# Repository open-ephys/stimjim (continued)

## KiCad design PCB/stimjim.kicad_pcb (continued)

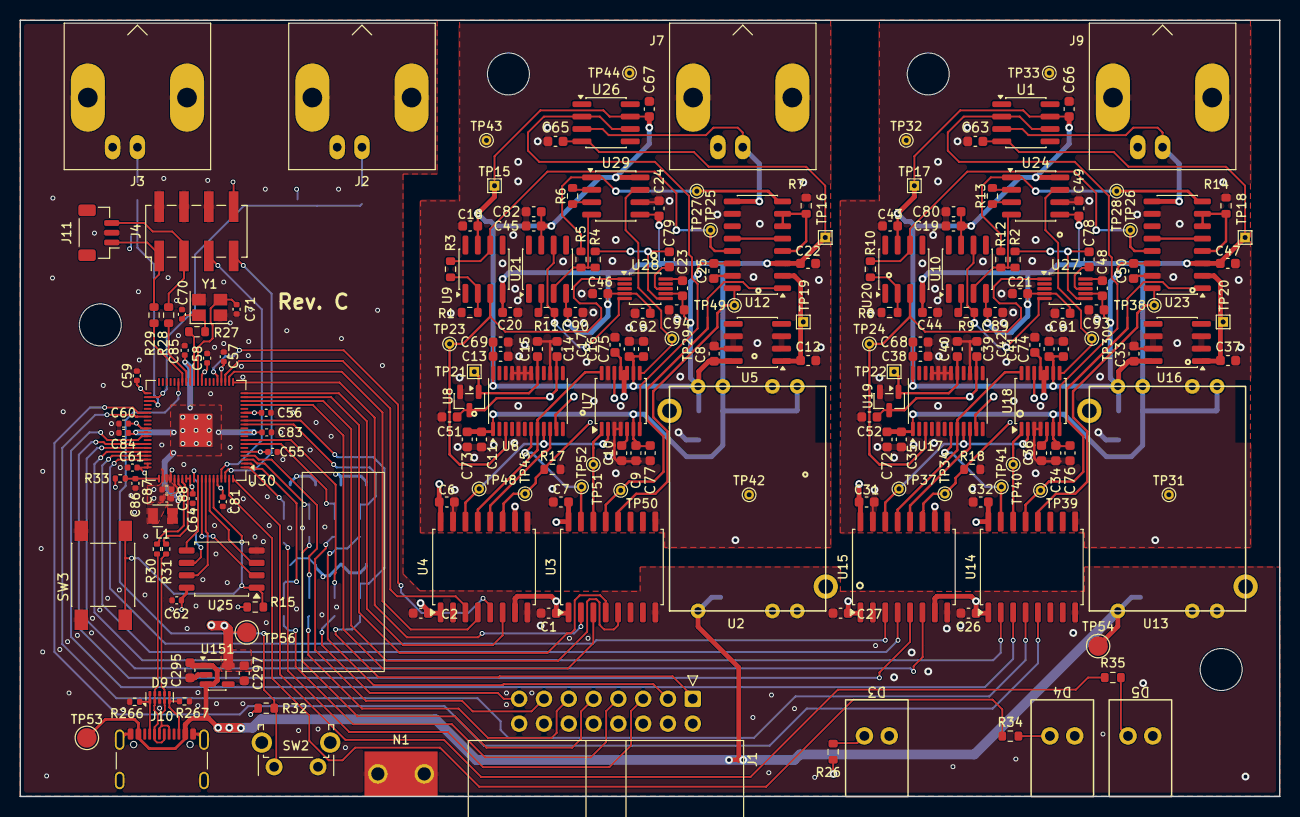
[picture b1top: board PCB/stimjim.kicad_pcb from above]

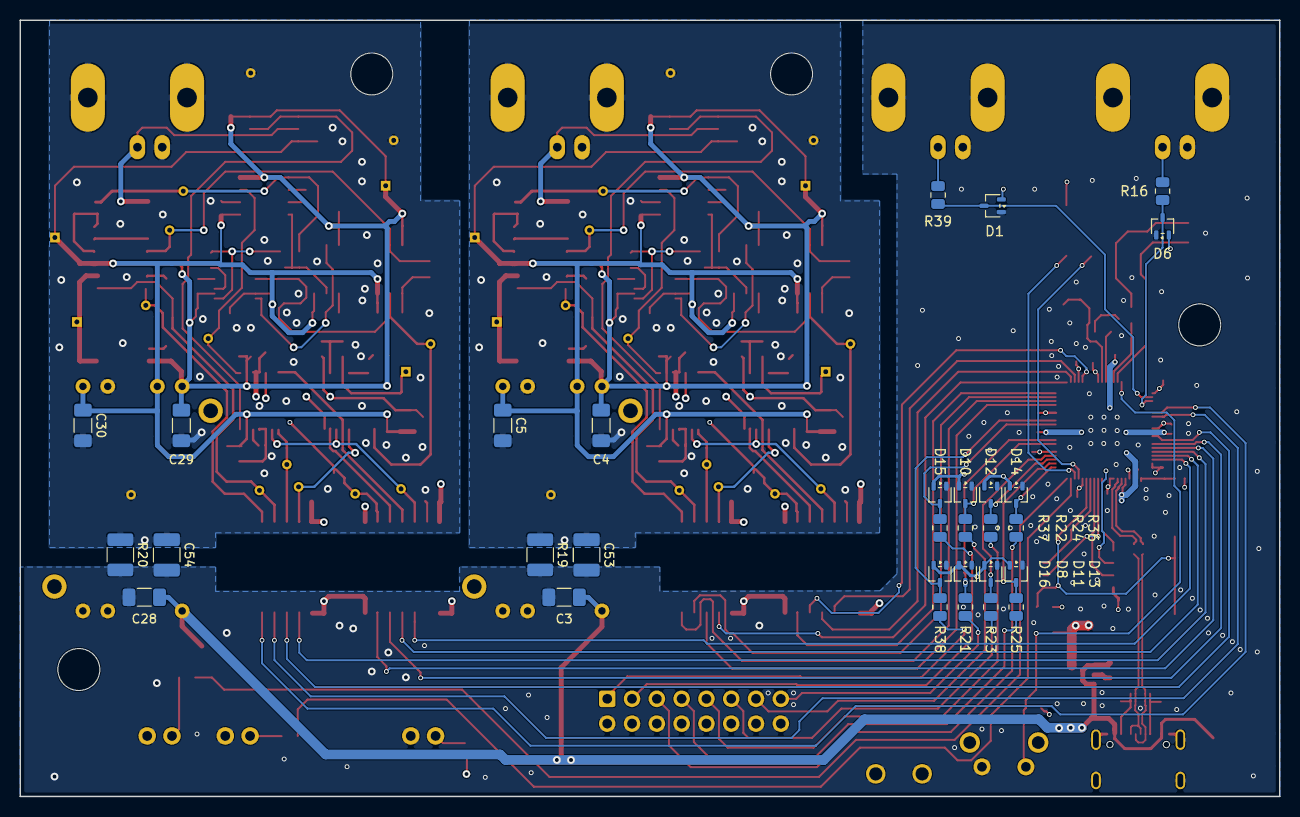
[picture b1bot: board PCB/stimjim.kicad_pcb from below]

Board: 4 copper layers, 129.0 x 79.5 mm, 235 parts (30 on the bottom side), 129 nets.

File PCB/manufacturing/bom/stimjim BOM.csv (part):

"#","Qty","Reference","Value","Tolerance","Footprint","TempCo","Voltage","DNP","OEPSPN","MPN","Description"
"1","40","C1,C2,C6,C7,C9,C11,C13,C14,C16,C17,C18,C20,C22,C23,C24,C25,C26,C27,C31,C32,C34,C35,C38,C39,C41,C42,C43,C44,C47,C48,C49,C50,C63,C65,C66,C67,C80,C82,C89,C90","0.1uF","","Capacitor_SMD:C_0603_1608Metric","","","","OEPS010009","GRM188R72A104KA35D","CAPACITOR:   SMD CER 0603 100nF 100V ±10% X7R   [GRM188R72A104KA35D] [SMD]"
"2","6","C3,C4,C5,C28,C29,C30","10uF","","Capacitor_SMD:C_1206_3216Metric_Pad1.33x1.80mm_HandSolder","","25V","","OEPS010094","GRT319R6YA106KE01D","CAPACITOR:   SMD CER 1206 10uF 35V ±10% X5R   [GRT319R6YA106KE01D] [SMD]"
"3","12","C8,C10,C12,C15,C33,C36,C37,C40,C51,C52,C295,C297","1uF","","Capacitor_SMD:C_0603_1608Metric","X5R","25V","","OEPS010022","CL10A105KA8NNNC","CAPACITOR:   SMD CER 0603 1uF 25V ±10% X5R   [CL10A105KA8NNNC] [SMD]"
"4","4","C19,C21,C45,C46","0.01uF","","Capacitor_SMD:C_0603_1608Metric","","","","OEPS010074","C1608X7R1H103K080AA","CAPACITOR:   SMD CER 0603 10nF 50V ±10% X7R   [C1608X7R1H103K080AA] [SMD]"
"5","2","C53,C54","2.2nF","","Capacitor_SMD:C_1210_3225Metric_Pad1.33x2.70mm_HandSolder","","","DNP","OEPS000000","DNP","DNP: Do Not Populate (DNI)"
"6","12","C55,C56,C57,C58,C59,C60,C61,C62,C64,C81,C83,C84","0.1uF","","Capacitor_SMD:C_0402_1005Metric","X7R","","","OEPS010050","C1005X7R1E104K050BB","CAPACITOR:   SMD CER 0402 100nF 25V ±10% X7R (OEPS H02 001)   [C1005X7R1E104K050BB] [SMD]"
"7","8","C68,C69,C72,C73,C74,C75,C76,C77","10uF","","Capacitor_SMD:C_0603_1608Metric","","","","OEPS010093","GRM188R6YA106MA73J","CAPACITOR:   SMD CER 0603 10uF 35V ±20% X5R   [GRM188R6YA106MA73J] [SMD]"
"8","2","C70,C71","22p","","Capacitor_SMD:C_0402_1005Metric","","","","OEPS010080","CL05C220JB51PNC","CAPACITOR:   SMD CER 0402 22pF 50V ±5% C0G/NP0   [CL05C220JB51PNC] [SMD]"
"9","2","C78,C79","10p","","Capacitor_SMD:C_0603_1608Metric","","","","OEPS010096","C0603C100J5GACTU","CAPACITOR:   SMD CER 0603 10pF 50V ±5% C0G   [C0603C100J5GACTU] [SMD]"
"10","4","C85,C86,C87,C88","4.7u","","Capacitor_SMD:C_0402_1005Metric","X5R","16V","","OEPS010097","KGM05CR51C475MH","CAPACITOR:   SMD CER 0402 4.7uF 16V ±20% X5R   [KGM05CR51C475MH] [SMD]"
"11","4","C91,C92,C93,C94","4.7u","","Capacitor_SMD:C_0603_1608Metric","","","","OEPS010047","GRM188R61E475KE11D","CAPACITOR:   SMD CER 0603 4.7uF 25V ±10% X5R (OEPS J05 009)   [GRM188R61E475KE11D] [SMD]"
"12","10","D1,D6,D8,D10,D11,D12,D13,D14,D15,D16","BAT54SW","","Package_TO_SOT_SMD:SOT-323_SC-70","","","","OEPS030056","BAT54SW","DIODE:   DIODE SCHOTTKY 30V 340mA ARRAY   [BAT54SW] [TH]"
"13","3","D3,D4,D5","LED","","open-ephys:LUMEX_SSF-LHXH100GD-01","","","","OEPS030055","SSF-LXH100GD-01","DIODE:   LED TH Green 565nm 20mA R/A   [SSF-LXH100GD-01] [TH]"
"14","1","D9","TPD4E05U06DQA","","Package_SON:USON-10_2.5x1.0mm_P0.5mm","","","","OEPS030037","TPD4E05U06DQAR","DIODE:   TVS DIODE 5.5VWM 14VC   [TPD4E05U06DQAR] [10-UFDFN]"
"15","1","J1","302-R161","","Connector_IDC:IDC-Header_2x08_P2.54mm_Horizontal","","","","OEPS070152","302-R161","CONNECTOR:   HEADER 2.54MM R/A 2x8POS   [302-R161] [TH]"
"16","4","J2,J3,J7,J9","0731375003","","Connector_Coaxial:BNC_Amphenol_B6252HB-NPP3G-50_Horizontal","","","","OEPS070151","0731375003","CONNECTOR:   BNC JACK 50ohm R/A   [0731375003] [TH]"
"17","1","J4","10129383-910002ALF","","Connector_PinHeader_2.54mm:PinHeader_2x04_P2.54mm_Vertical_SMD","","","DNP","OEPS070120","10129383-910002ALF","CONNECTOR:   HEADER VERT 2x5POS 2.54MM   [10129383-910002ALF] [SMD]"
"18","1","J10","USB4105-GF-A","","Connector_USB:USB_C_Receptacle_GCT_USB4105-xx-A_16P_TopMnt_Horizontal","","","","OEPS070105","USB4105-GF-A","CONNECTOR:   USB2.0 TYPE C 16P SMD R/A   [USB4105-GF-A] [SMD/TH]"
"19","1","J11","BM03B-SRSS-TB","","Connector_JST:JST_SH_BM03B-SRSS-TB_1x03-1MP_P1.00mm_Vertical","","","DNP","OEPS070121","BM03B-SRSS-TB","CONNECTOR:   HEADER VERT 3POS 1MM   [BM03B-SRSS-TB] [SMD]"
"20","1","L1","AOTA-B201610S3R3-101-T","","open-ephys:L_Abracon_2x1.6x1.0mm","","","","OEPS040036","AOTA-B201610S3R3-101-T","INDUCTOR:   FIXED INDUCTOR SMD 3.3uH 2.1A 140mΩ   [AOTA-B201610S3R3-101-T] [0806]"
"21","1","N1","SMTRAM3-7-5ET","","open-ephys:SMTRA_M3-7-5ET","","","","OEPS100089","SMTRAM3-7-5ET","OTHER:   SURFACE MOUNT R'ANGLE M3   [SMTRAM3-7-5ET] [Other]"
"22","2","R1,R8","5k","0.1%","Resistor_SMD:R_0603_1608Metric","","","","OEPS020263","RT0603BRE075KL","RESISTOR:   SMD 0603 5kΩ ±0.1% 0.100W   [RT0603BRE075KL] [SMD]"
"23","2","R2,R4","1.5k","0.1%","Resistor_SMD:R_0603_1608Metric","","","","OEPS020262","RG1608P-152-B-T5","RESISTOR:   SMD 0603 1.5kΩ ±0.1% 0.100W   [RG1608P-152-B-T5] [SMD]"
"24","2","R3,R10","10k","0.1%","Resistor_SMD:R_0603_1608Metric","","","","OEPS020235","RG1608P-103-B-T5","RESISTOR:   SMD 0603 10kΩ ±0.1% 0.100W   [RG1608P-103-B-T5] [SMD]"
"25","2","R5,R12","100","0.1%","Resistor_SMD:R_0603_1608Metric","","","","OEPS020232","RG1608P-101-B-T5","RESISTOR:   SMD 0603 100Ω ±0.1% 0.100W   [RG1608P-101-B-T5] [SMD]"
"26","2","R6,R13","1.8k","0.1%","Resistor_SMD:R_0603_1608Metric","","","","OEPS020261","RG1608P-182-B-T5 ","RESISTOR:   SMD 0603 1.8kΩ ±0.1% 0.100W   [RG1608P-182-B-T5] [SMD]"
"27","3","R7,R14,R27","1k","1%","Resistor_SMD:R_0603_1608Metric","","","","OEPS020215","RG1608P-102-B-T5","RESISTOR:   SMD 0603 1kΩ ±0.1% 0.100W   [RG1608P-102-B-T5] [SMD]"
"28","2","R9,R11","0","","Resistor_SMD:R_0603_1608Metric","","","","OEPS020151","RCS06030000Z0EA","RESISTOR:   SMD 0603 0Ω 1A   [RCS06030000Z0EA] [SMD]"
"29","4","R15,R17,R18,R32","10k","","Resistor_SMD:R_0603_1608Metric","","","","OEPS020133","RC0603FR-0710KL","RESISTOR:   SMD 0603 10kΩ ±1% 0.100W   [RC0603FR-0710KL] [SMD]"
"30","10","R16,R21,R22,R23,R24,R25,R36,R37,R38,R39","270","","Resistor_SMD:R_0805_2012Metric","","","","OEPS020024","CRCW0805270RFKEAHP","RESISTOR:   SMD 0805 270Ω ±1% 0.500W   [CRCW0805270RFKEAHP] [SMD]"
"31","2","R19,R20","2.2M","","Resistor_SMD:R_1210_3225Metric_Pad1.30x2.65mm_HandSolder","","","","OEPS020230","CRGCQ1210J2M2","RESISTOR:   SMD 1210 2.2MΩ ±5% 0.5W   [CRGCQ1210J2M2] [SMD]"
"32","3","R26,R34,R35","200","","Resistor_SMD:R_0603_1608Metric","","","","OEPS020141","RC0603FR-07200RL","RESISTOR:   SMD 0603 200Ω ±1% 0.100W (OEPS J30 017)   [RC0603FR-07200RL] [SMD]"
"33","2","R28,R29","100","1%","Resistor_SMD:R_0603_1608Metric","","","","OEPS020042","CRCW0603100RFKEAHP","RESISTOR:   SMD 0603 100Ω ±1% 0.333W   [CRCW0603100RFKEAHP] [SMD]"
"34","3","R30,R31,R33","27","","Resistor_SMD:R_0402_1005Metric","","","","OEPS020170","RMCF0402FT27R0","RESISTOR:   SMD 0402 27Ω ±1% 0.063W   [RMCF0402FT27R0] [SMD]"
"35","2","R266,R267","5.1k","1%","Resistor_SMD:R_0402_1005Metric","","","","OEPS020173","ERJ-2RKF5101X","RESISTOR:   SMD 0402 5.1kΩ ±1% 0.100W   [ERJ-2RKF5101X] [SMD]"
"36","1","SW2","PTS645VH58-2 LFS","","Button_Switch_THT:SW_Tactile_SPST_Angled_PTS645Vx58-2LFS","","","","OEPS070114","PTS645VH58-2 LFS","CONNECTOR:   SWITCH TACTILE SPST-NO 0.05A 12V   [PTS645VH58-2 LFS] [TH]"
"37","1","SW3","TS04-66-50-BK-160-SMT","","open-ephys:SAMESKY_TS04-66-XX-BK-XXX-SMT-XX","","","","OEPS070115","TS04-66-50-BK-160-SMT","CONNECTOR:   SWITCH TACTILE SPST-NO TOP ACTUATED   [TS04-66-50-BK-160-SMT] [SMD]"
"38","6","U1,U9,U10,U20,U21,U26","OPA197","","Package_SO:SOIC-8_3.9x4.9mm_P1.27mm","","","","OEPS080229","OPA197IDR","IC:   OPAMP GP 1 CIRCUIT   [OPA197IDR] [8-SOIC]"
"39","2","U2,U13","CC3-0512DF-E","","microstim:CC3-0512DF-E","","","","OEPS100043","CC3-0512DF-E","OTHER:   DC DC CONVERTER +/-12V TO +/-15V 3W   [CC3-0512DF-E] [Populated PCB]"
"40","2","U3,U14","ISO7760","","Package_SO:SOIC-16W_7.5x10.3mm_P1.27mm","","","","OEPS080228","ISO7760DWR","IC:   DIGITAL ISOLATOR 6 Channel    [ISO7760DWR] [16-SOIC]"
"41","2","U4,U15","ISO7741","","Package_SO:SOIC-16W_7.5x10.3mm_P1.27mm","","","","OEPS080227","ISO7741DWR","IC:   DIGITAL ISOLATOR 4 Channel    [ISO7741DWR] [16-SOIC]"
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
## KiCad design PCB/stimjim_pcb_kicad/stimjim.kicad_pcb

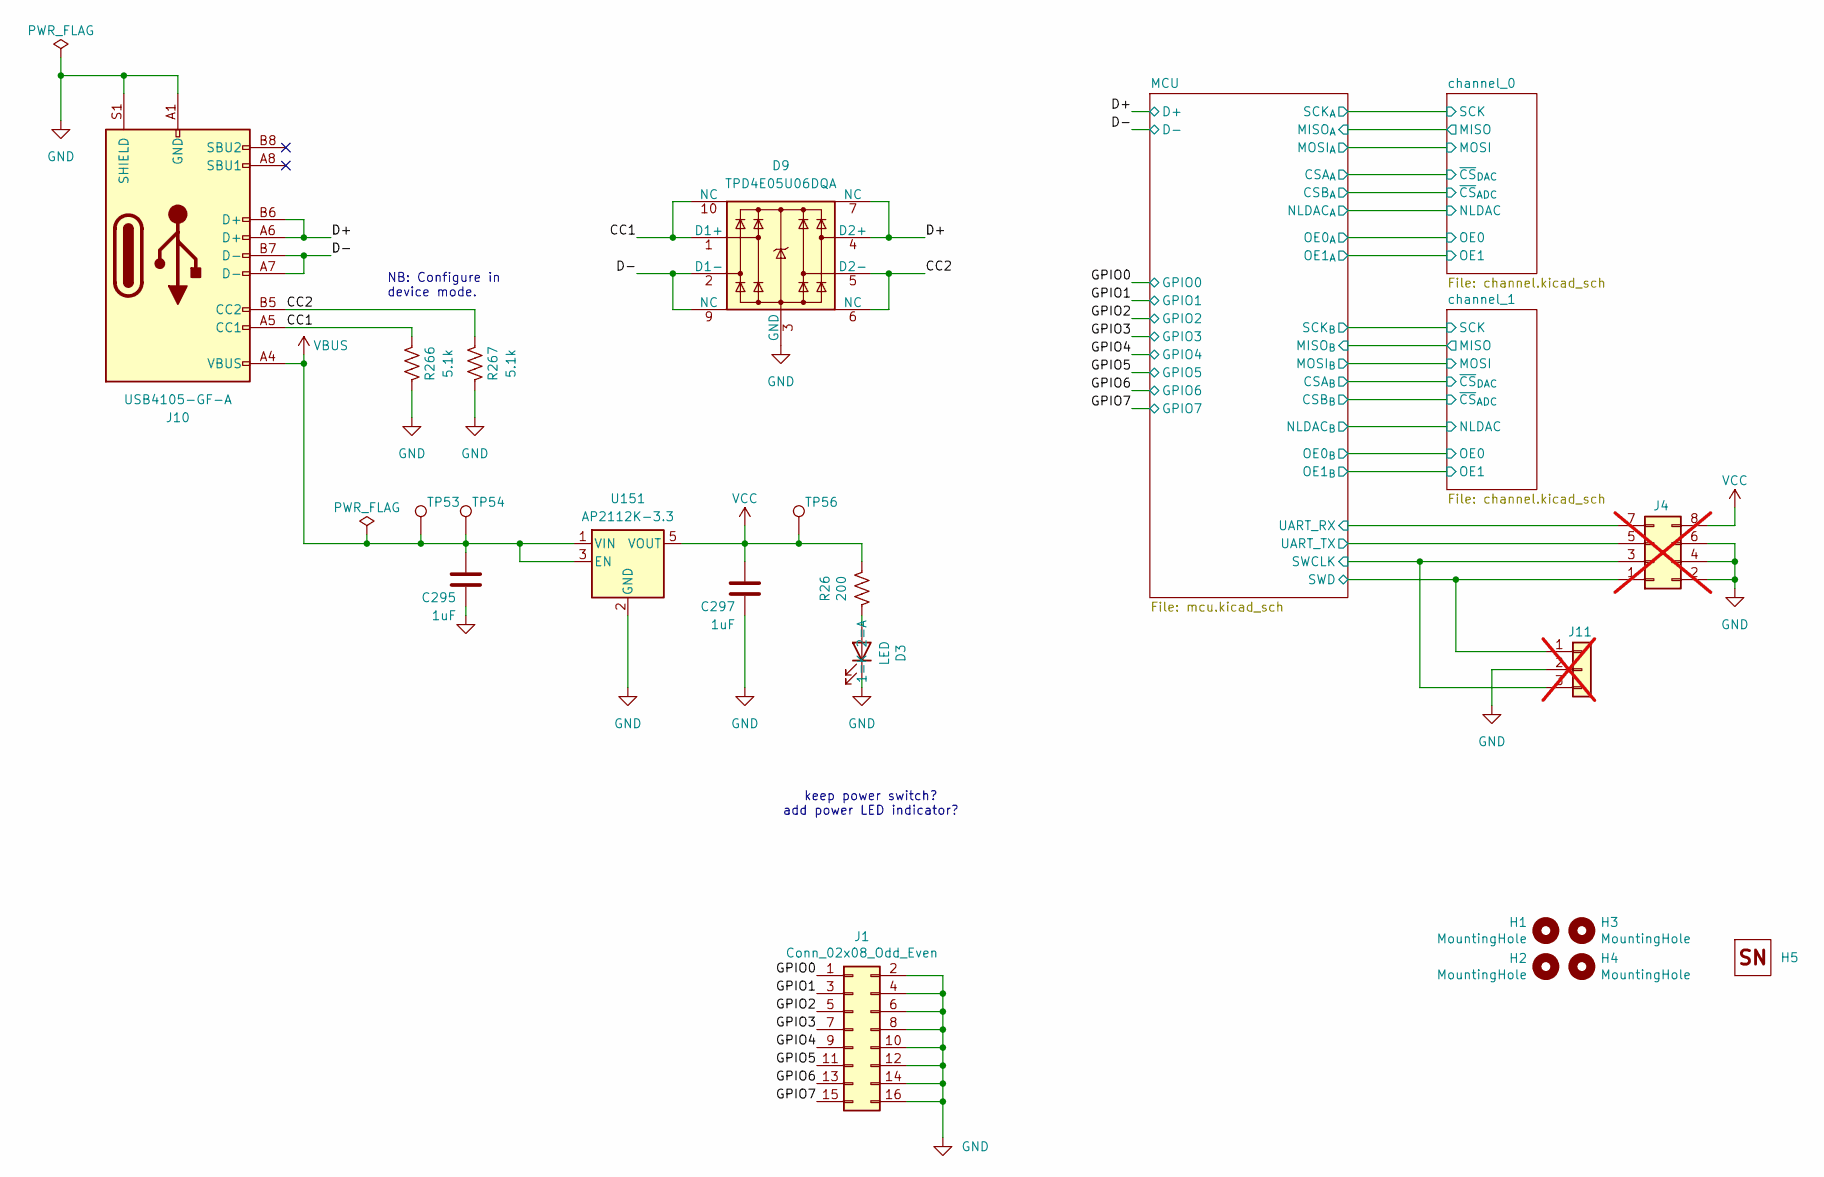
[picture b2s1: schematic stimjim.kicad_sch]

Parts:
C295, C297: 1uF; C_0603_1608Metric; Voltage 16V
D3: LED; LED_D5.0mm_Horizontal_O1.27mm_Z3.0mm_pinSwapped
D9: TPD4E05U06DQA; USON-10_2.5x1.0mm_P0.5mm
H1, H2, H3, H4: MountingHole; MountingHole_4.3mm_M4
H5: OEPS_SN-STICKER-8x20mm
J1: Conn_02x08_Odd_Even; IDC-Header_2x08_P2.54mm_Horizontal
J4: 10129383-910002ALF; PinHeader_2x04_P2.54mm_Vertical_SMD; not fitted
J10: USB4105-GF-A; USB_C_Receptacle_GCT_USB4105-xx-A_16P_TopMnt_Horizontal
J11: BM03B-SRSS-TB; JST_SH_BM03B-SRSS-TB_1x03-1MP_P1.00mm_Vertical; not fitted
R26: 200; R_0603_1608Metric
R266, R267: 5.1k; R_0402_1005Metric
TP53, TP54: GND; TestPoint_Pad_D2.0mm
TP56: VCC; TestPoint_Pad_D2.0mm
U151: AP2112K-3.3; SOT-23-5

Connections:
/CC1: D9.1 (D1+), D9.10 (NC), J10.A5 (CC1), R266.1
/CC2: D9.5 (D2-), D9.6 (NC), J10.B5 (CC2), R267.1
/D+: D9.4 (D2+), D9.7 (NC), J10.A6 (D+), J10.B6 (D+); also elsewhere on the board
/D-: D9.2 (D1-), D9.9 (NC), J10.A7 (D-), J10.B7 (D-); also elsewhere on the board
/GPIO0: J1.1; also elsewhere on the board
/GPIO1: J1.3; also elsewhere on the board
/GPIO2: J1.5; also elsewhere on the board
/GPIO3: J1.7; also elsewhere on the board
/GPIO4: J1.9; also elsewhere on the board
/GPIO5: J1.11; also elsewhere on the board
/GPIO6: J1.13; also elsewhere on the board
/GPIO7: J1.15; also elsewhere on the board
/MCU/SWCLK: J4.3, J11.3; also elsewhere on the board
/MCU/SWD: J4.1, J11.1; also elsewhere on the board
/MCU/UART_RX: J4.7; also elsewhere on the board
/MCU/UART_TX: J4.5; also elsewhere on the board
GND: C295.2, C297.2, D3.1 (K), D9.3 (GND), D9.8 (GND), J1.2, J1.4, J1.6, J1.8, J1.10, J1.12, J1.14, J1.16, J4.2, J4.4, J4.6, J10.A1 (GND), J10.A12 (GND), J10.B1 (GND), J10.B12 (GND), J10.S1 (SHIELD), J11.2, R266.2, R267.2, U151.2 (GND); also elsewhere on the board
unnamed: D3.2 (A), R26.2
VBUS: C295.1, J10.A4 (VBUS), J10.A9 (VBUS), J10.B4 (VBUS), J10.B9 (VBUS), TP53.1, TP54.1, U151.1 (VIN), U151.3 (EN); also elsewhere on the board
VCC: C297.1, J4.8, R26.1, TP56.1, U151.5 (VOUT); also elsewhere on the board

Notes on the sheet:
NB: Configure in device mode.
keep power switch? add power LED indicator?

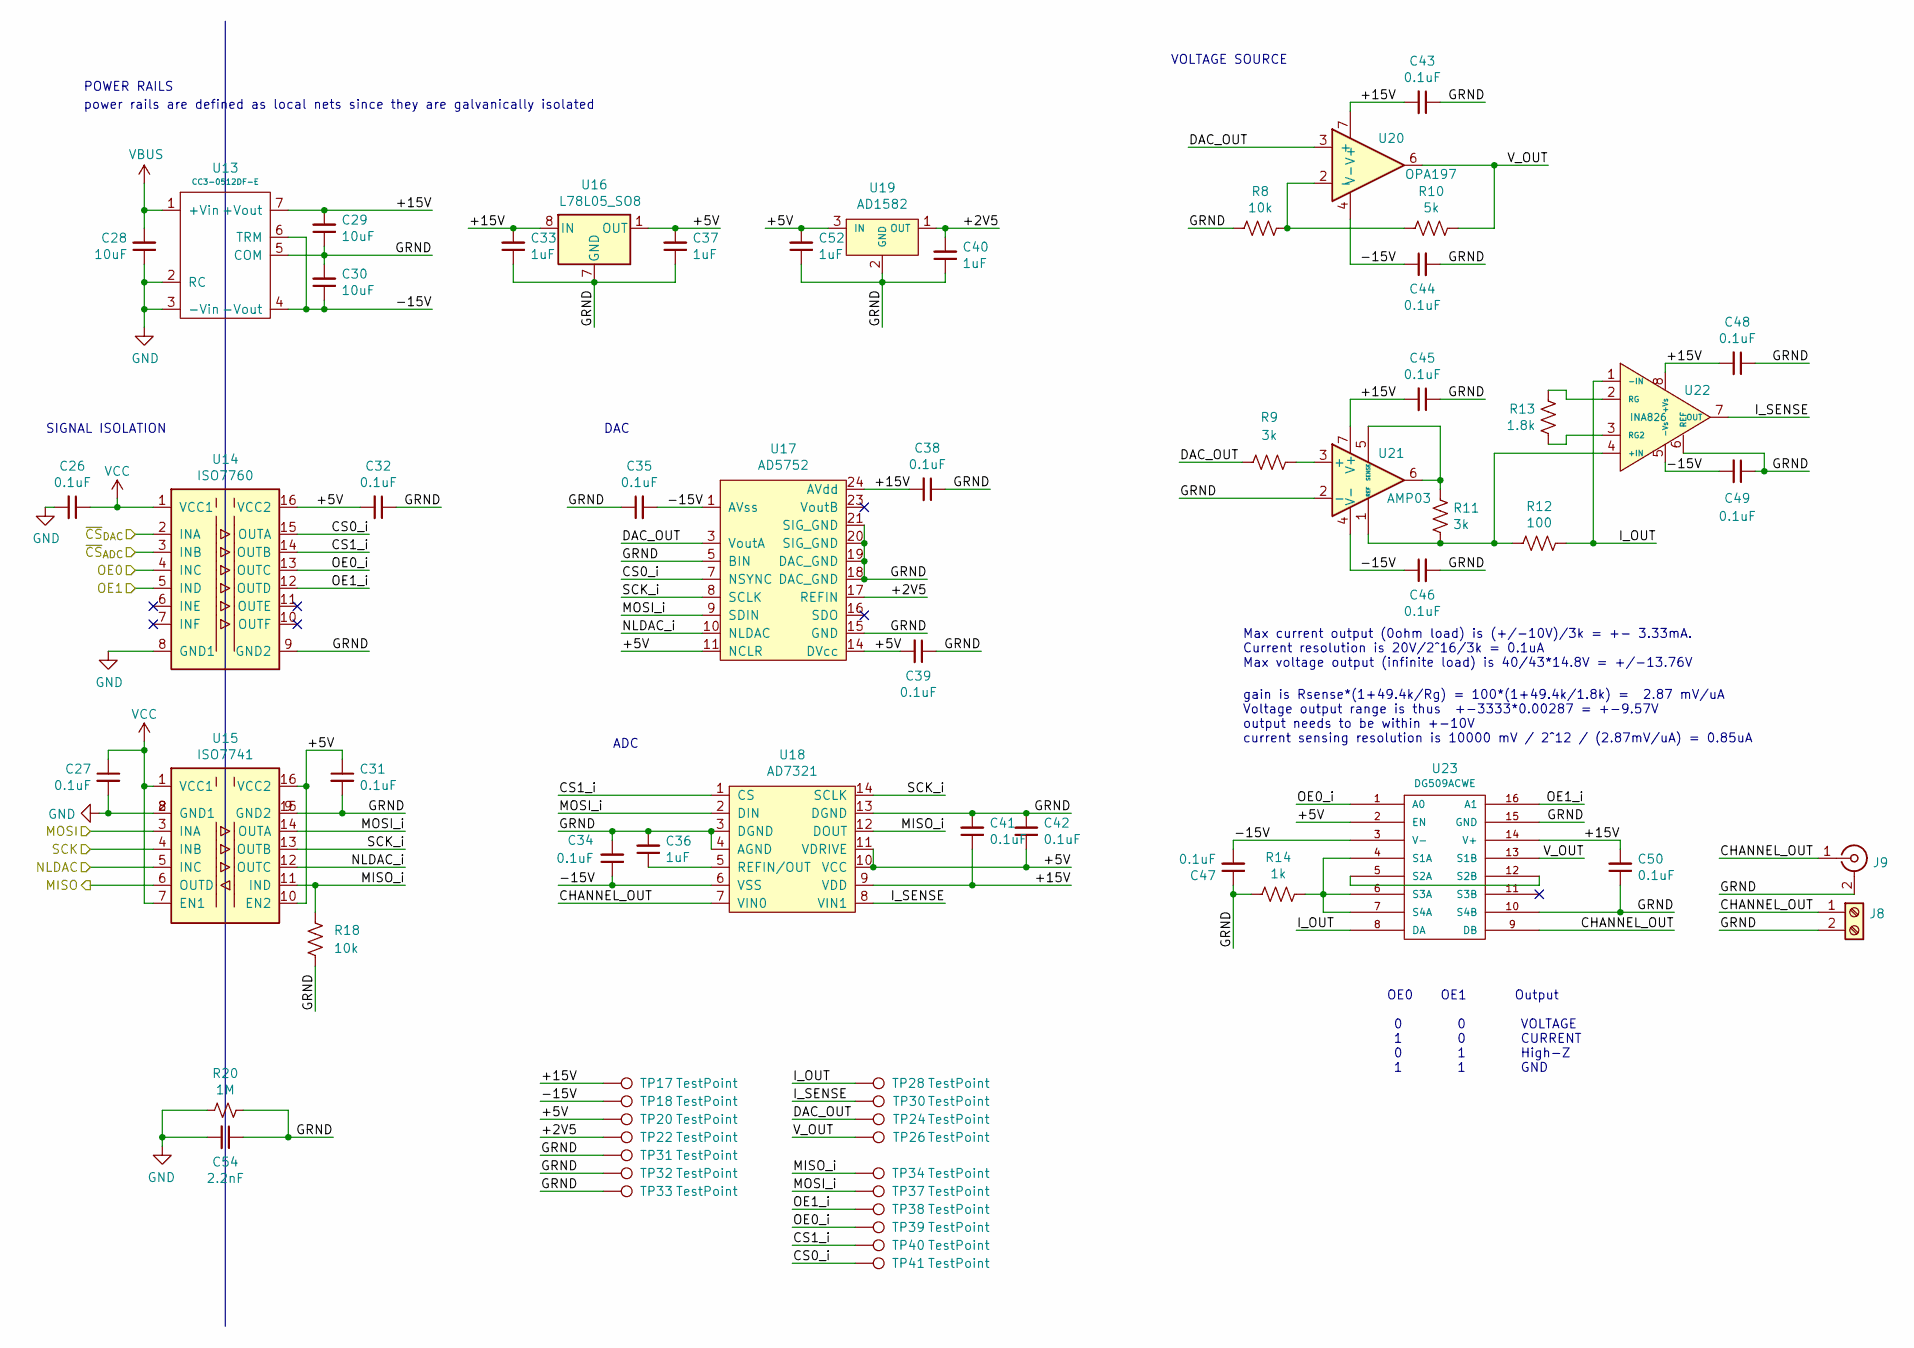
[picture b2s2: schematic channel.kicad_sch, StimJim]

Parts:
C26, C27, C31, C32, C34, C35, C38, C39, C41, C42, C43, C44, C45, C46, C47, C48, C49, C50: 0.1uF; C_0603_1608Metric
C28, C29, C30: 10uF; C_1206_3216Metric_Pad1.33x1.80mm_HandSolder
C33, C36, C37, C40, C52: 1uF; C_0603_1608Metric
C54: 2.2nF; C_1210_3225Metric_Pad1.33x2.70mm_HandSolder
J8: Screw_Terminal_01x02; 1-2834016-2 _TERM_BLK_2P_SIDE_ENT_2.54MM_PCB
J9: Conn_Coaxial; BNC_Amphenol_B6252HB-NPP3G-50_Horizontal
R8, R18: 10k; R_0603_1608Metric
R9, R11: 3k; R_0603_1608Metric
R10: 5k; R_0603_1608Metric
R12: 100; R_0603_1608Metric
R13: 1.8k; R_0603_1608Metric
R14: 1k; R_0603_1608Metric
R20: 1M; R_1210_3225Metric_Pad1.30x2.65mm_HandSolder
TP17, TP18, TP20, TP22: TestPoint; TestPoint_THTPad_1.0x1.0mm_Drill0.5mm
TP24, TP26, TP28, TP30, TP31, TP32, TP33, TP34, TP37, TP38, TP39, TP40, TP41: TestPoint; TestPoint_THTPad_D1.0mm_Drill0.5mm
U13: CC3-0512DF-E
U14: ISO7760; SOIC-16W_7.5x10.3mm_P1.27mm
U15: ISO7741; SOIC-16W_7.5x10.3mm_P1.27mm
U16: L78L05_SO8; SOIC-8_3.9x4.9mm_P1.27mm
U17: AD5752; TSSOP-24_4.4x7.8mm_P0.65mm
U18: AD7321; TSSOP-14_4.4x5mm_P0.65mm
U19: AD1582; SOT-23
U20: OPA197; SOIC-8_3.9x4.9mm_P1.27mm
U21: AMP03; SOIC-8_3.9x4.9mm_P1.27mm
U22: INA826; SOIC-8_3.9x4.9mm_P1.27mm
U23: DG509ACWE; SO-16_3.9x9.9mm_P1.27mm

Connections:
/MCU/CSA_{A}: U14.2 (INA); also elsewhere on the board
/MCU/CSB_{A}: U14.3 (INB); also elsewhere on the board
/MCU/MISO_{A}: U15.6 (OUTD); also elsewhere on the board
/MCU/MOSI_{A}: U15.3 (INA); also elsewhere on the board
/MCU/NLDAC_{A}: U15.5 (INC); also elsewhere on the board
/MCU/OE0_{A}: U14.4 (INC); also elsewhere on the board
/MCU/OE1_{A}: U14.5 (IND); also elsewhere on the board
/MCU/SCK_{A}: U15.4 (INB); also elsewhere on the board
/channel_0/+2V5: C40.2, TP22.1, U17.17 (REFIN), U19.1 (OUT)
/channel_0/+5V: C31.1, C32.2, C37.2, C39.2, C42.1, C52.2, TP20.1, U14.16 (VCC2), U15.10 (EN2), U15.16 (VCC2), U16.1 (OUT), U17.11 (NCLR), U17.14 (DVcc), U18.10 (VCC), U18.11 (VDRIVE), U19.3 (IN), U23.2 (EN)
/channel_0/+15V: C29.2, C33.2, C38.2, C41.1, C43.2, C45.2, C48.2, C50.2, TP17.1, U13.7 (+Vout), U16.8 (IN), U17.24 (AVdd), U18.9 (VDD), U20.7 (V+), U21.7 (V+), U22.8 (+Vs), U23.14 (V+)
/channel_0/-15V: C30.1, C34.1, C35.2, C44.1, C46.1, C47.2, C49.2, TP18.1, U13.4 (-Vout), U13.6 (TRM), U17.1 (AVss), U18.6 (VSS), U20.4 (V-), U21.4 (V-), U22.5 (-Vs), U23.3 (V-)
/channel_0/CHANNEL_OUT: J8.1, J9.1 (In), U18.7 (VIN0), U23.9 (DB)
/channel_0/CS0_i: TP41.1, U14.15 (OUTA), U17.7 (NSYNC)
/channel_0/CS1_i: TP40.1, U14.14 (OUTB), U18.1 (CS)
/channel_0/DAC_OUT: R9.2, TP24.1, U17.3 (VoutA), U20.3 (+)
/channel_0/GRND: C29.1, C30.2, C31.2, C32.1, C33.1, C34.2, C35.1, C36.2, C37.1, C38.1, C39.1, C40.1, C41.2, C42.2, C43.1, C44.2, C45.1, C46.2, C47.1, C48.1, C49.1, C50.1, C52.1, C54.1, J8.2, J9.2 (Ext), R8.1, R14.1, R18.1, R20.1, TP31.1, TP32.1, TP33.1, U13.5 (COM), U14.9 (GND2), U15.9 (GND2), U15.15 (GND2), U16.2 (GND), U16.3 (GND), U16.6 (GND), U16.7 (GND), U17.5 (BIN), U17.15 (GND), U17.18 (DAC_GND), U17.19 (DAC_GND), U17.20 (SIG_GND), U17.21 (SIG_GND), U18.3 (DGND), U18.4 (AGND), U18.13 (DGND), U19.2 (GND), U21.2 (-), U22.6 (REF), U23.10 (S4B), U23.15 (GND)
/channel_0/I_OUT: R12.2, TP28.1, U22.1 (-IN), U23.8 (DA)
/channel_0/I_SENSE: TP30.1, U18.8 (VIN1), U22.7 (OUT)
/channel_0/MISO_i: R18.2, TP34.1, U15.11 (IND), U18.12 (DOUT)
/channel_0/MOSI_i: TP37.1, U15.14 (OUTA), U17.9 (SDIN), U18.2 (DIN)
/channel_0/NLDAC_i: U15.12 (OUTC), U17.10 (NLDAC)
/channel_0/OE0_i: TP39.1, U14.13 (OUTC), U23.1 (A0)
/channel_0/OE1_i: TP38.1, U14.12 (OUTD), U23.16 (A1)
/channel_0/SCK_i: U15.13 (OUTB), U17.8 (SCLK), U18.14 (SCLK)
/channel_0/V_OUT: R10.2, TP26.1, U20.6, U23.13 (S1B)
GND: C26.2, C27.2, C28.1, C54.2, R20.2, U13.2 (RC), U13.3 (-Vin), U14.8 (GND1), U15.2 (GND1), U15.8 (GND1); also elsewhere on the board
unnamed: C36.1, U18.5 (REFIN/OUT)
unnamed: R8.2, R10.1, U20.2 (-)
unnamed: R9.1, U21.3 (+)
unnamed: R11.1, R12.1, U21.1 (REF), U22.4 (+IN)
unnamed: R11.2, U21.5 (SENSE), U21.6
unnamed: R13.1, U22.3 (RG2)
unnamed: R13.2, U22.2 (RG)
unnamed: R14.2, U23.4 (S1A), U23.6 (S3A), U23.7 (S4A)
unnamed: U23.5 (S2A), U23.12 (S2B)
VBUS: C28.2, U13.1 (+Vin); also elsewhere on the board
VCC: C26.1, C27.1, U14.1 (VCC1), U15.1 (VCC1), U15.7 (EN1); also elsewhere on the board

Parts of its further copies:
C1, C2, C6, C7, C9, C11, C13, C14, C16, C17, C18, C19, C20, C21, C22, C23, C24, C25: 0.1uF; C_0603_1608Metric
C3, C4, C5: 10uF; C_1206_3216Metric_Pad1.33x1.80mm_HandSolder
C8, C10, C12, C15, C51: 1uF; C_0603_1608Metric
C53: 2.2nF; C_1210_3225Metric_Pad1.33x2.70mm_HandSolder
J6: Screw_Terminal_01x02; 1-2834016-2 _TERM_BLK_2P_SIDE_ENT_2.54MM_PCB
J7: Conn_Coaxial; BNC_Amphenol_B6252HB-NPP3G-50_Horizontal
R1, R17: 10k; R_0603_1608Metric
R2, R4: 3k; R_0603_1608Metric
R3: 5k; R_0603_1608Metric
R5: 100; R_0603_1608Metric
R6: 1.8k; R_0603_1608Metric
R7: 1k; R_0603_1608Metric
R19: 1M; R_1210_3225Metric_Pad1.30x2.65mm_HandSolder
TP15, TP16, TP19, TP21: TestPoint; TestPoint_THTPad_1.0x1.0mm_Drill0.5mm
TP23, TP25, TP27, TP29, TP42, TP43, TP44, TP45, TP48, TP49, TP50, TP51, TP52: TestPoint; TestPoint_THTPad_D1.0mm_Drill0.5mm
U2: CC3-0512DF-E
U3: ISO7760; SOIC-16W_7.5x10.3mm_P1.27mm
U4: ISO7741; SOIC-16W_7.5x10.3mm_P1.27mm
U5: L78L05_SO8; SOIC-8_3.9x4.9mm_P1.27mm
U6: AD5752; TSSOP-24_4.4x7.8mm_P0.65mm
U7: AD7321; TSSOP-14_4.4x5mm_P0.65mm
U8: AD1582; SOT-23
U9: OPA197; SOIC-8_3.9x4.9mm_P1.27mm
U10: AMP03; SOIC-8_3.9x4.9mm_P1.27mm
U11: INA826; SOIC-8_3.9x4.9mm_P1.27mm
U12: DG509ACWE; SO-16_3.9x9.9mm_P1.27mm

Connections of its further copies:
/MCU/CSA_{B}: U3.2 (INA); also elsewhere on the board
/MCU/CSB_{B}: U3.3 (INB); also elsewhere on the board
/MCU/MISO_{B}: U4.6 (OUTD); also elsewhere on the board
/MCU/MOSI_{B}: U4.3 (INA); also elsewhere on the board
/MCU/NLDAC_{B}: U4.5 (INC); also elsewhere on the board
/MCU/OE0_{B}: U3.4 (INC); also elsewhere on the board
/MCU/OE1_{B}: U3.5 (IND); also elsewhere on the board
/MCU/SCK_{B}: U4.4 (INB); also elsewhere on the board
/channel_1/+2V5: C15.2, TP21.1, U6.17 (REFIN), U8.1 (OUT)
/channel_1/+5V: C6.1, C7.2, C12.2, C14.2, C17.1, C51.2, TP19.1, U3.16 (VCC2), U4.10 (EN2), U4.16 (VCC2), U5.1 (OUT), U6.11 (NCLR), U6.14 (DVcc), U7.10 (VCC), U7.11 (VDRIVE), U8.3 (IN), U12.2 (EN)
/channel_1/+15V: C4.2, C8.2, C13.2, C16.1, C18.2, C19.2, C23.2, C25.2, TP15.1, U2.7 (+Vout), U5.8 (IN), U6.24 (AVdd), U7.9 (VDD), U9.7 (V+), U10.7 (V+), U11.8 (+Vs), U12.14 (V+)
/channel_1/-15V: C5.1, C9.1, C11.2, C20.1, C21.1, C22.2, C24.2, TP16.1, U2.4 (-Vout), U2.6 (TRM), U6.1 (AVss), U7.6 (VSS), U9.4 (V-), U10.4 (V-), U11.5 (-Vs), U12.3 (V-)
/channel_1/CHANNEL_OUT: J6.1, J7.1 (In), U7.7 (VIN0), U12.9 (DB)
/channel_1/CS0_i: TP52.1, U3.15 (OUTA), U6.7 (NSYNC)
/channel_1/CS1_i: TP51.1, U3.14 (OUTB), U7.1 (CS)
/channel_1/DAC_OUT: R2.2, TP23.1, U6.3 (VoutA), U9.3 (+)
/channel_1/GRND: C4.1, C5.2, C6.2, C7.1, C8.1, C9.2, C10.2, C11.1, C12.1, C13.1, C14.1, C15.1, C16.2, C17.2, C18.1, C19.1, C20.2, C21.2, C22.1, C23.1, C24.1, C25.1, C51.1, C53.1, J6.2, J7.2 (Ext), R1.1, R7.1, R17.1, R19.1, TP42.1, TP43.1, TP44.1, U2.5 (COM), U3.9 (GND2), U4.9 (GND2), U4.15 (GND2), U5.2 (GND), U5.3 (GND), U5.6 (GND), U5.7 (GND), U6.5 (BIN), U6.15 (GND), U6.18 (DAC_GND), U6.19 (DAC_GND), U6.20 (SIG_GND), U6.21 (SIG_GND), U7.3 (DGND), U7.4 (AGND), U7.13 (DGND), U8.2 (GND), U10.2 (-), U11.6 (REF), U12.10 (S4B), U12.15 (GND)
/channel_1/I_OUT: R5.2, TP27.1, U11.1 (-IN), U12.8 (DA)
/channel_1/I_SENSE: TP29.1, U7.8 (VIN1), U11.7 (OUT)
/channel_1/MISO_i: R17.2, TP45.1, U4.11 (IND), U7.12 (DOUT)
/channel_1/MOSI_i: TP48.1, U4.14 (OUTA), U6.9 (SDIN), U7.2 (DIN)
/channel_1/NLDAC_i: U4.12 (OUTC), U6.10 (NLDAC)
/channel_1/OE0_i: TP50.1, U3.13 (OUTC), U12.1 (A0)
/channel_1/OE1_i: TP49.1, U3.12 (OUTD), U12.16 (A1)
/channel_1/SCK_i: U4.13 (OUTB), U6.8 (SCLK), U7.14 (SCLK)
/channel_1/V_OUT: R3.2, TP25.1, U9.6, U12.13 (S1B)
GND: C1.2, C2.2, C3.1, C53.2, R19.2, U2.2 (RC), U2.3 (-Vin), U3.8 (GND1), U4.2 (GND1), U4.8 (GND1); also elsewhere on the board
unnamed: C10.1, U7.5 (REFIN/OUT)
unnamed: R1.2, R3.1, U9.2 (-)
unnamed: R2.1, U10.3 (+)
unnamed: R4.1, R5.1, U10.1 (REF), U11.4 (+IN)
unnamed: R4.2, U10.5 (SENSE), U10.6
unnamed: R6.1, U11.3 (RG2)
unnamed: R6.2, U11.2 (RG)
unnamed: R7.2, U12.4 (S1A), U12.6 (S3A), U12.7 (S4A)
unnamed: U12.5 (S2A), U12.12 (S2B)
VBUS: C3.2, U2.1 (+Vin); also elsewhere on the board
VCC: C1.1, C2.1, U3.1 (VCC1), U4.1 (VCC1), U4.7 (EN1); also elsewhere on the board

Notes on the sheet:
power rails are defined as local nets since they are galvanically isolated
ADC
gain is Rsense*(1+49.4k/Rg) = 100*(1+49.4k/1.8k) = 2.87 mV/uA Voltage output range is thus +-3333*0.00287 = +-9.57V output needs to be within +-10V current sensing resolution is 10000 mV / 2^12 / (2.87mV/uA) = 0.85uA
OE0 OE1 Output 0 0 VOLTAGE 1 0 CURRENT 0 1 High-Z 1 1 GND
SIGNAL ISOLATION
POWER RAILS
VOLTAGE SOURCE
DAC
Max current output (0ohm load) is (+/-10V)/3k = +- 3.33mA. Current resolution is 20V/2^16/3k = 0.1uA Max voltage output (infinite load) is 40/43*14.8V = +/-13.76V

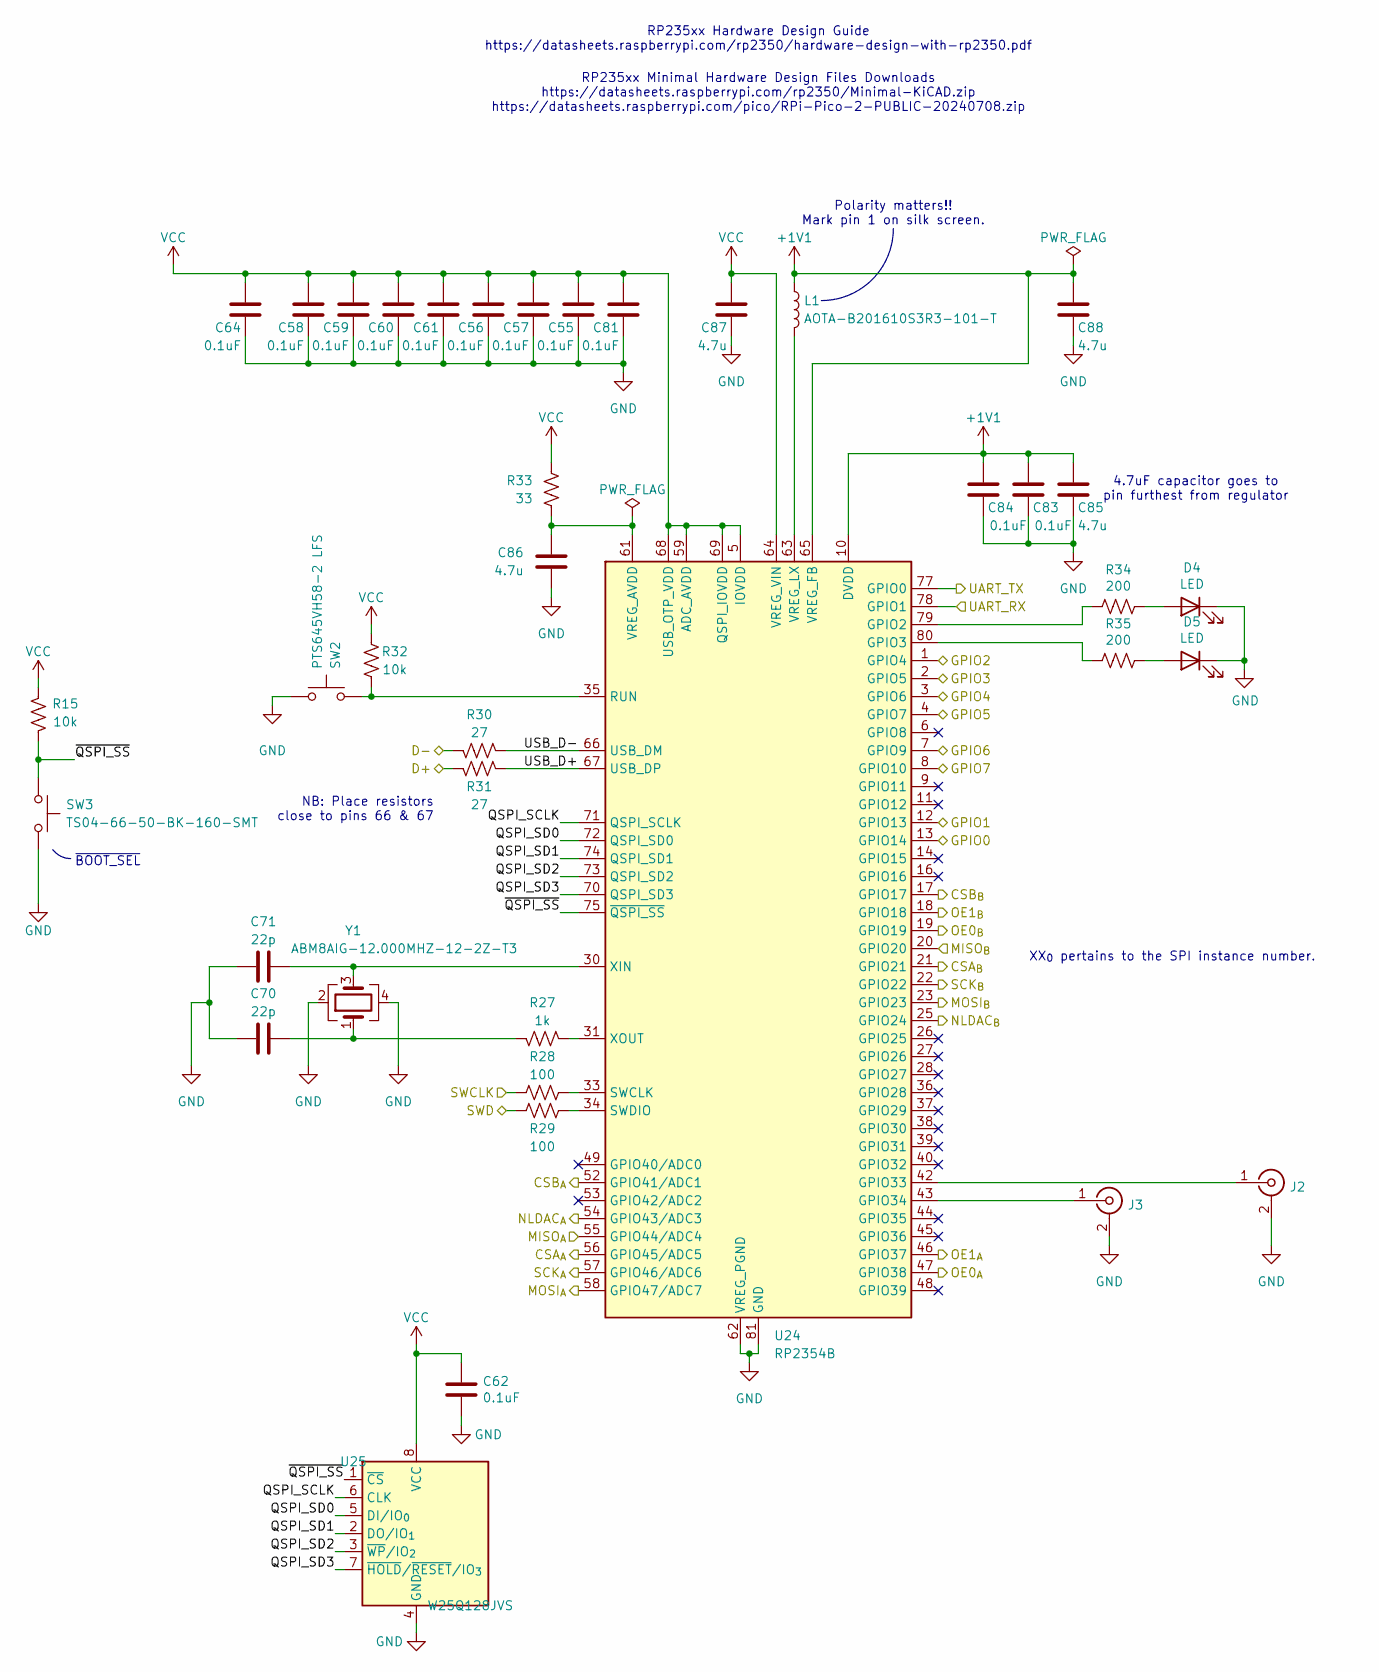
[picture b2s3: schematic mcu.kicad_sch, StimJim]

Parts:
C55, C56, C57, C58, C59, C60, C61, C62, C64, C81, C83, C84: 0.1uF; C_0402_1005Metric
C70, C71: 22p; C_0402_1005Metric
C85, C87, C88: 4.7u; C_0402_1005Metric; Voltage 16V
C86: 4.7u; C_0402_1005Metric
D4, D5: LED; LED_D5.0mm_Horizontal_O1.27mm_Z3.0mm_pinSwapped
J2, J3: Conn_Coaxial; BNC_Amphenol_B6252HB-NPP3G-50_Horizontal
L1: AOTA-B201610S3R3-101-T; L_Abracon_2x1.6x1.0mm
R15, R32: 10k; R_0402_1005Metric
R27: 1k; R_0402_1005Metric
R28, R29: 100; R_0402_1005Metric
R30, R31: 27; R_0402_1005Metric
R33: 33; R_0402_1005Metric
R34, R35: 200; R_0603_1608Metric
SW2: PTS645VH58-2 LFS; SW_Tactile_SPST_Angled_PTS645Vx58-2LFS
SW3: TS04-66-50-BK-160-SMT; SW_SPST_PTS645Sx43SMTR92
U24: RP2354B; QFN-80-1EP_10x10mm_P0.4mm_EP3.4x3.4mm_ThermalVias
U25: W25Q128JVS; SOIC-8_5.3x5.3mm_P1.27mm
Y1: ABM8AIG-12.000MHZ-12-2Z-T3; Crystal_SMD_Abracon_ABM8AIG-4Pin_3.2x2.5mm

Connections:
+1V1: C83.1, C84.1, C85.1, C88.1, L1.1, U24.10 (DVDD), U24.32 (DVDD), U24.51 (DVDD), U24.65 (VREG_FB)
/D+: R31.2; also elsewhere on the board
/D-: R30.2; also elsewhere on the board
/GPIO0: U24.13 (GPIO14); also elsewhere on the board
/GPIO1: U24.12 (GPIO13); also elsewhere on the board
/GPIO2: U24.1 (GPIO4); also elsewhere on the board
/GPIO3: U24.2 (GPIO5); also elsewhere on the board
/GPIO4: U24.3 (GPIO6); also elsewhere on the board
/GPIO5: U24.4 (GPIO7); also elsewhere on the board
/GPIO6: U24.7 (GPIO9); also elsewhere on the board
/GPIO7: U24.8 (GPIO10); also elsewhere on the board
/MCU/CSA_{A}: U24.56 (GPIO45/ADC5); also elsewhere on the board
/MCU/CSA_{B}: U24.21 (GPIO21); also elsewhere on the board
/MCU/CSB_{A}: U24.52 (GPIO41/ADC1); also elsewhere on the board
/MCU/CSB_{B}: U24.17 (GPIO17); also elsewhere on the board
/MCU/MISO_{A}: U24.55 (GPIO44/ADC4); also elsewhere on the board
/MCU/MISO_{B}: U24.20 (GPIO20); also elsewhere on the board
/MCU/MOSI_{A}: U24.58 (GPIO47/ADC7); also elsewhere on the board
/MCU/MOSI_{B}: U24.23 (GPIO23); also elsewhere on the board
/MCU/NLDAC_{A}: U24.54 (GPIO43/ADC3); also elsewhere on the board
/MCU/NLDAC_{B}: U24.25 (GPIO24); also elsewhere on the board
/MCU/OE0_{A}: U24.47 (GPIO38); also elsewhere on the board
/MCU/OE0_{B}: U24.19 (GPIO19); also elsewhere on the board
/MCU/OE1_{A}: U24.46 (GPIO37); also elsewhere on the board
/MCU/OE1_{B}: U24.18 (GPIO18); also elsewhere on the board
/MCU/QSPI_SCLK: U24.71 (QSPI_SCLK), U25.6 (CLK)
/MCU/QSPI_SD0: U24.72 (QSPI_SD0), U25.5 (DI/IO_{0})
/MCU/QSPI_SD1: U24.74 (QSPI_SD1), U25.2 (DO/IO_{1})
/MCU/QSPI_SD2: U24.73 (QSPI_SD2), U25.3 (~WP/IO_{2})
/MCU/QSPI_SD3: U24.70 (QSPI_SD3), U25.7 (~HOLD/~RESET/IO_{3})
/MCU/SCK_{A}: U24.57 (GPIO46/ADC6); also elsewhere on the board
/MCU/SCK_{B}: U24.22 (GPIO22); also elsewhere on the board
/MCU/SWCLK: R28.1; also elsewhere on the board
/MCU/SWD: R29.1; also elsewhere on the board
/MCU/UART_RX: U24.78 (GPIO1); also elsewhere on the board
/MCU/UART_TX: U24.77 (GPIO0); also elsewhere on the board
/MCU/USB_D+: R31.1, U24.67 (USB_DP)
/MCU/USB_D-: R30.1, U24.66 (USB_DM)
/MCU/~QSPI_SS: R15.2, SW3.2, U24.75 (~QSPI_SS), U25.1 (~CS)
GND: C55.2, C56.2, C57.2, C58.2, C59.2, C60.2, C61.2, C62.2, C64.2, C70.1, C71.1, C81.2, C83.2, C84.2, C85.2, C86.2, C87.2, C88.2, D4.1 (K), D5.1 (K), J2.2 (Ext), J3.2 (Ext), SW2.1, SW3.1, U24.62 (VREG_PGND), U24.81 (GND), U25.4 (GND), Y1.2, Y1.4; also elsewhere on the board
unnamed: C70.2, R27.2, Y1.1
unnamed: D4.2 (A), R34.1
unnamed: D5.2 (A), R35.1
unnamed: J2.1 (In), U24.42 (GPIO33)
unnamed: J3.1 (In), U24.43 (GPIO34)
unnamed: R34.2, U24.79 (GPIO2)
unnamed: R35.2, U24.80 (GPIO3)
unnamed: R32.2, SW2.2, U24.35 (RUN)
unnamed: R28.2, U24.33 (SWCLK)
unnamed: R29.2, U24.34 (SWDIO)
unnamed: C86.1, R33.2, U24.61 (VREG_AVDD)
unnamed: L1.2, U24.63 (VREG_LX)
unnamed: C71.2, U24.30 (XIN), Y1.3
unnamed: R27.1, U24.31 (XOUT)
VCC: C55.1, C56.1, C57.1, C58.1, C59.1, C60.1, C61.1, C62.1, C64.1, C81.1, C87.1, R15.1, R32.1, R33.1, U24.5 (IOVDD), U24.15 (IOVDD), U24.24 (IOVDD), U24.29 (IOVDD), U24.41 (IOVDD), U24.50 (IOVDD), U24.59 (ADC_AVDD), U24.60 (IOVDD), U24.64 (VREG_VIN), U24.68 (USB_OTP_VDD), U24.69 (QSPI_IOVDD), U24.76 (IOVDD), U25.8 (VCC); also elsewhere on the board

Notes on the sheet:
Polarity matters!! Mark pin 1 on silk screen.
RP235xx Minimal Hardware Design Files Downloads https://datasheets.raspberrypi.com/rp2350/Minimal-KiCAD.zip https://datasheets.raspberrypi.com/pico/RPi-Pico-2-PUBLIC-20240708.zip
~{BOOT_SEL}
NB: Place resistors close to pins 66 & 67
RP235xx Hardware Design Guide https://datasheets.raspberrypi.com/rp2350/hardware-design-with-rp2350.pdf
4.7uF capacitor goes to pin furthest from regulator
XX_{0} pertains to the SPI instance number.
